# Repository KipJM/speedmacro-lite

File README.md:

# speedmacro-lite
**A small macropad with a similar key layout to the Davinci Resolve speed editor.**

Includes a rotary encoder (no click) and an OLED screen.

The key layout is designed to mimic a combination of the left and middle part of a Davinci Resolve speed editor, with two 1.5u "in" "out" point buttons at the top and a long 3u "play/pause" button at the bottom, with stabilizers. ergobleds are included with each key, plus a row of additional lighting is added at the top.

# CAD Model

The case is made up of two parts, the bottom carrier and the top plate. M3 16mm bolts are designed to thread through the entire sandwich assembly and act as adjustable feet for the macropad.

# Schematics
This macro pad uses a matrix wiring model, however caution that the electrical arrangement of switches do not match the actual physical location of the switches, because of the 2-3-3-1 switch layout this board uses.

## Firmware
SpeedMacro lite uses QMK firmware, but feel free to use other firmware platforms.
A minimal sample firmware build is provided.

## Bill of Materials
- 9x Cherry MX Switches
- 9x Cherry MX hotswap sockets
- 6x 1u DSA keycaps
- 2x 1.5u DSA keycaps
- 1x 3u DSA keycap (with stabs)
- 1x 3u stabs
- 4x M3x16mm SHCS Bolts
- 9x 1N4148 DO-35 Diodes
- 16x SK6812 MINI-E LEDs
- (optional) 4x M3x5mx4mm heatset inserts
- 1x 0.91in OLED Display
- 1x EC11 Rotary Encoder
- 1x 3D-printed case (2 parts)
- 1x Custom Printed Circuit Board
- 1x SEEED Studio XIAO RP2040

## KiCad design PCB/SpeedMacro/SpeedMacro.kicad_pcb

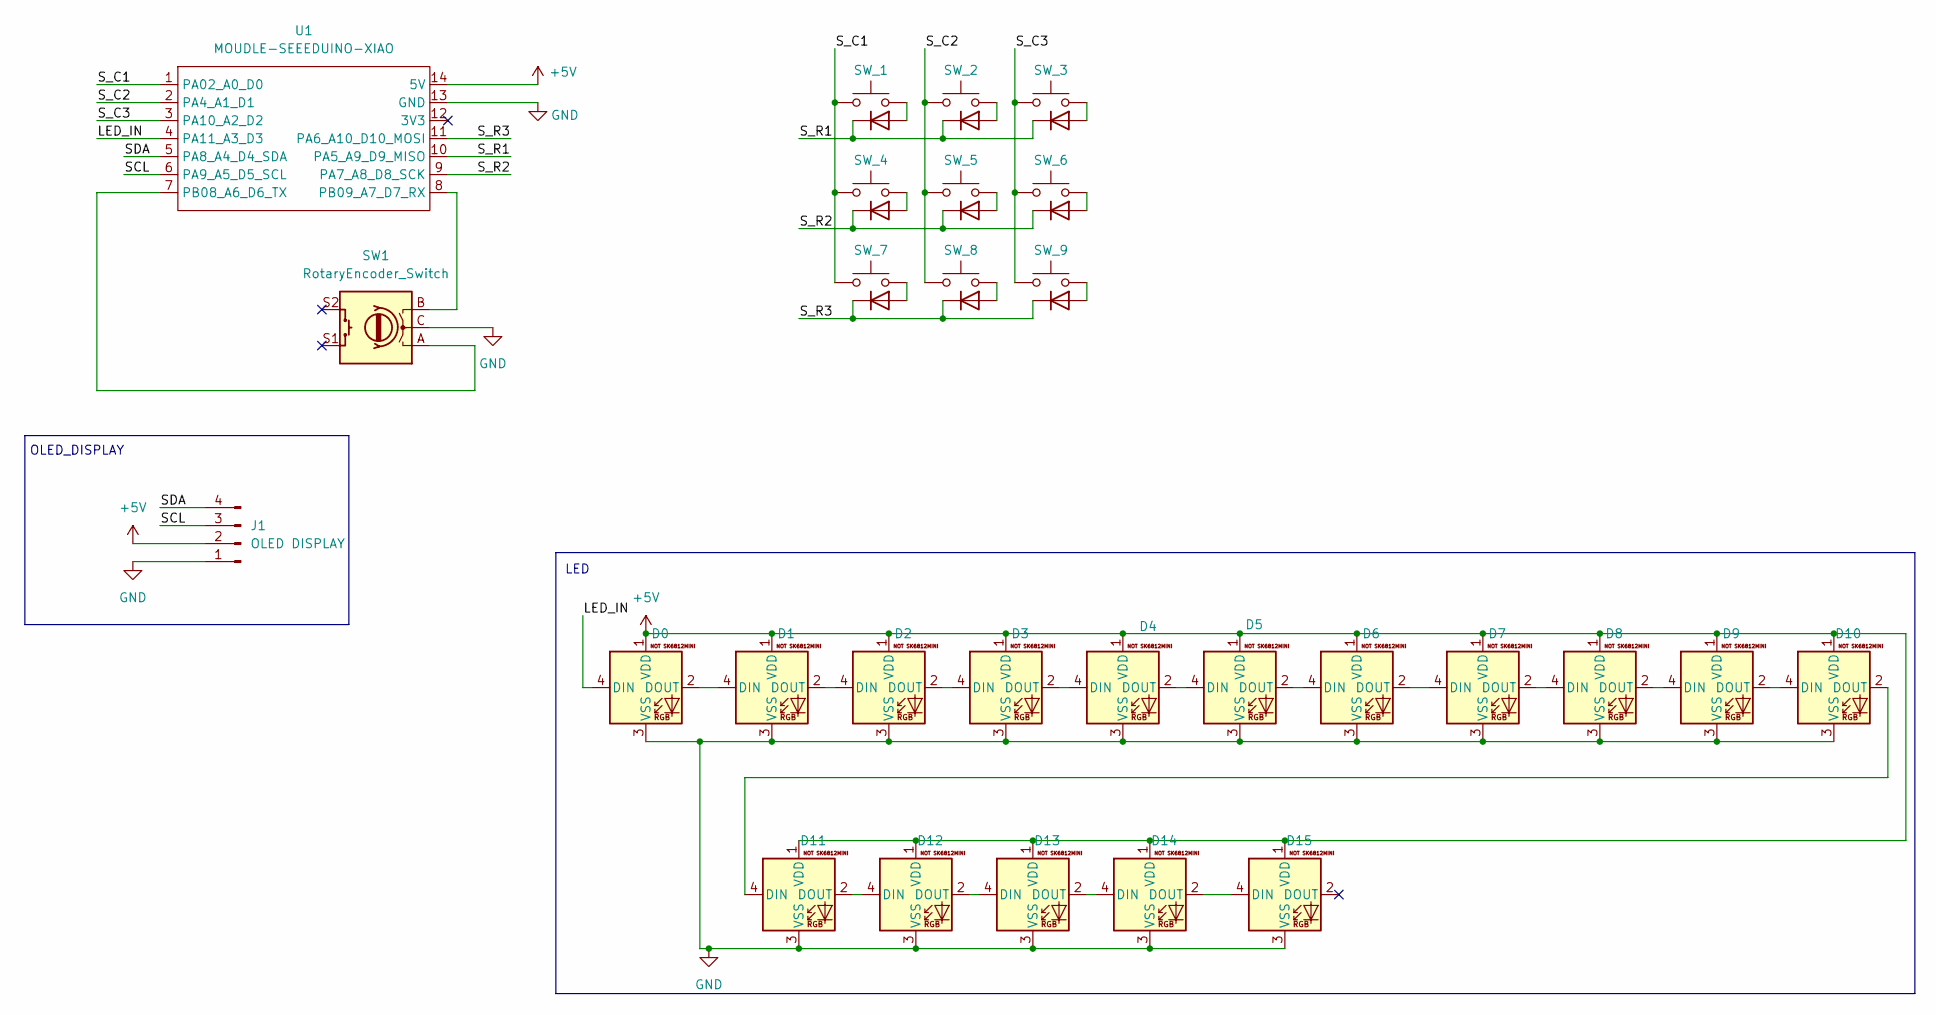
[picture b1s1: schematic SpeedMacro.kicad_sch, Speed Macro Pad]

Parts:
D0, D1, D2, D3, D4, D5, D6, D7, D8, D9, D10, D11, D12, D13, D14, D15: SK6812MINI-E; SK6812MINI-E_fixed
D16, D17, D18, D19, D20, D22, D23, D24, D28: 1N4148; D_DO-35_SOD27_P7.62mm_Horizontal
J1: OLED DISPLAY; PinHeader_1x04_P2.54mm_Vertical
SW1: RotaryEncoder_Switch; RotaryEncoder_Alps_EC11E-Switch_Vertical_H20mm
SW_1, SW_2, SW_3, SW_4, SW_5, SW_6, SW_7, SW_8, SW_9: SW_Push; SW_Hotswap_Kailh_MX_1.00u
U1: MOUDLE-SEEEDUINO-XIAO; XIAO-Generic-Hybrid-14P-2.54-21X17.8MM

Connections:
+5V: D0.1 (VDD), D1.1 (VDD), D2.1 (VDD), D3.1 (VDD), D4.1 (VDD), D5.1 (VDD), D6.1 (VDD), D7.1 (VDD), D8.1 (VDD), D9.1 (VDD), D10.1 (VDD), D11.1 (VDD), D12.1 (VDD), D13.1 (VDD), D14.1 (VDD), D15.1 (VDD), J1.2, U1.14 (5V)
/LED_IN: D0.4 (DIN), U1.4 (PA11_A3_D3)
/SCL: J1.3, U1.6 (PA9_A5_D5_SCL)
/SDA: J1.4, U1.5 (PA8_A4_D4_SDA)
/S_C1: SW_1.1, SW_4.1, SW_7.1, U1.1 (PA02_A0_D0)
/S_C2: SW_2.1, SW_5.1, SW_8.1, U1.2 (PA4_A1_D1)
/S_C3: SW_3.1, SW_6.1, SW_9.1, U1.3 (PA10_A2_D2)
/S_R1: D16.1 (K), D17.1 (K), D19.1 (K), U1.10 (PA5_A9_D9_MISO)
/S_R2: D18.1 (K), D20.1 (K), D23.1 (K), U1.9 (PA7_A8_D8_SCK)
/S_R3: D22.1 (K), D24.1 (K), D28.1 (K), U1.11 (PA6_A10_D10_MOSI)
GND: D0.3 (VSS), D1.3 (VSS), D2.3 (VSS), D3.3 (VSS), D4.3 (VSS), D5.3 (VSS), D6.3 (VSS), D7.3 (VSS), D8.3 (VSS), D9.3 (VSS), D10.3 (VSS), D11.3 (VSS), D12.3 (VSS), D13.3 (VSS), D14.3 (VSS), D15.3 (VSS), J1.1, SW1.C, U1.13 (GND)
unnamed: D0.2 (DOUT), D1.4 (DIN)
unnamed: D1.2 (DOUT), D2.4 (DIN)
unnamed: D2.2 (DOUT), D3.4 (DIN)
unnamed: D3.2 (DOUT), D4.4 (DIN)
unnamed: D4.2 (DOUT), D5.4 (DIN)
unnamed: D5.2 (DOUT), D6.4 (DIN)
unnamed: D6.2 (DOUT), D7.4 (DIN)
unnamed: D7.2 (DOUT), D8.4 (DIN)
unnamed: D8.2 (DOUT), D9.4 (DIN)
unnamed: D9.2 (DOUT), D10.4 (DIN)
unnamed: D10.2 (DOUT), D11.4 (DIN)
unnamed: D11.2 (DOUT), D12.4 (DIN)
unnamed: D12.2 (DOUT), D13.4 (DIN)
unnamed: D13.2 (DOUT), D14.4 (DIN)
unnamed: D14.2 (DOUT), D15.4 (DIN)
unnamed: D16.2 (A), SW_1.2
unnamed: D17.2 (A), SW_3.2
unnamed: D18.2 (A), SW_4.2
unnamed: D19.2 (A), SW_2.2
unnamed: D20.2 (A), SW_6.2
unnamed: D22.2 (A), SW_7.2
unnamed: D23.2 (A), SW_5.2
unnamed: D24.2 (A), SW_9.2
unnamed: D28.2 (A), SW_8.2
unnamed: SW1.A, U1.7 (PB08_A6_D6_TX)
unnamed: SW1.B, U1.8 (PB09_A7_D7_RX)

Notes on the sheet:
LED
OLED_DISPLAY

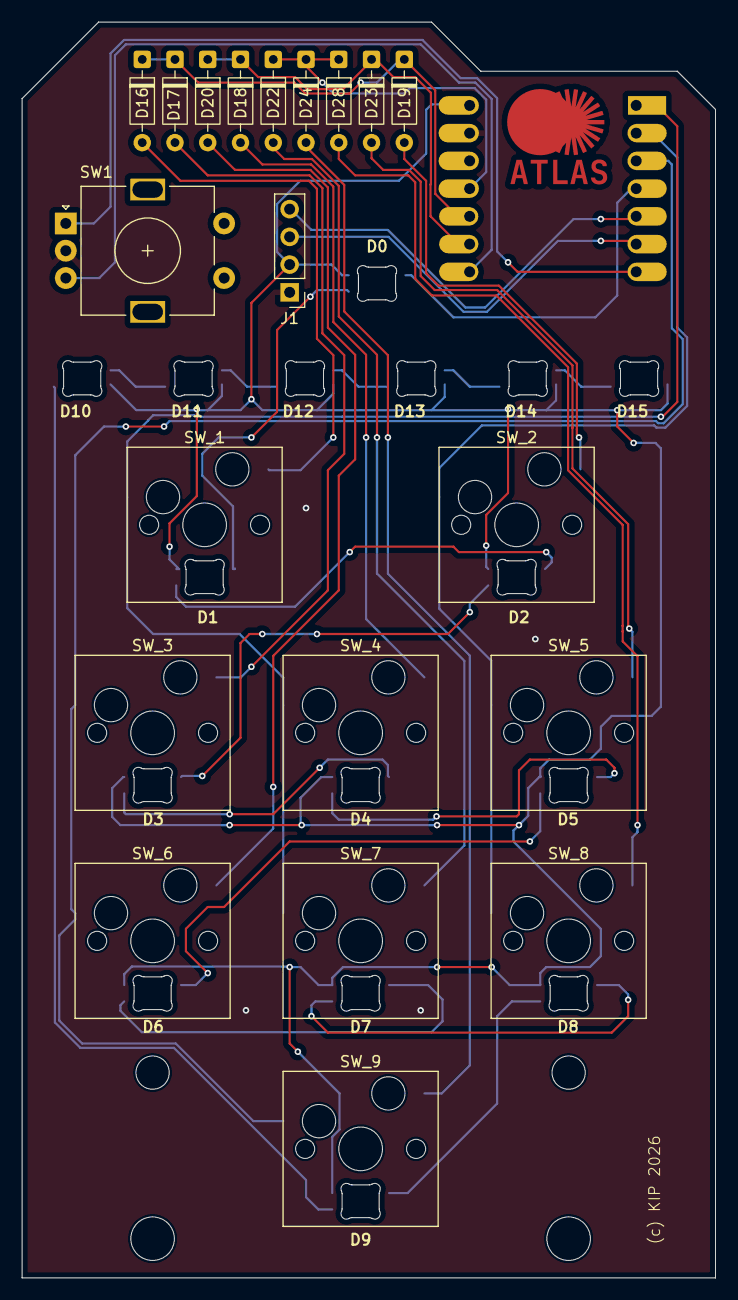
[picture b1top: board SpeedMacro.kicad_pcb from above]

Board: 2 copper layers, 63.5 x 114.9 mm, 38 parts (1 on the bottom side), 37 nets.

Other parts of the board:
LOGO: LOGO

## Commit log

2026-03-26 Initial Submit
    Added V1 revision files.
